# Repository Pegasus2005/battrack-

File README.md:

# 🏏 BatTrack — Universal Sports Implement Tracker

> **PCB Status: ✅ 39/39 connectivity checks passed — Fabrication ready**

A compact, open-source motion tracker for **cricket bats, baseball bats, badminton rackets, pickleball paddles**, tennis rackets, squash rackets, hockey sticks, and all bat/racket sports implements.

## ✅ Verified Connections (39/39)

| Block | Connections | Status |
|:---|:---|:---|
| USB-C (J1) | VBUS→VUSB, D+→USB_DP, D-→USB_DM, CC1/CC2 pulldowns | ✅ All 11 |
| TP4054 Charger (U3) | VUSB→pin4, VBAT→pin3, GND→pin2, CHRG_STAT, PROG | ✅ All 9 |
| SPI Bus (U1↔U2) | SCK, MISO, MOSI, CS, INT1 — all with F↔B vias | ✅ All 5 |
| WS2812B LED (D1) | VDD→VBAT, GND, DIN→LED_GPIO, DOUT→NC | ✅ All 4 |
| Power/Control | CHIP_EN, BTN_GPIO, ANT_RF, CC pulldowns | ✅ All 5 |
| Board specs | 22×16mm rect, 0.8mm, 2L, GND pour ×2 | ✅ All 4 |

---

## 📐 Hardware Overview

| Spec | Value |
|:---|:---|
| Board size | 22 × 16mm (+ 2mm USB-C slot) |
| Layers | 2-layer PCB |
| Thickness | 0.8mm FR4 |
| MCU | ESP32-C3FN4 (RISC-V, BLE 5.0, USB built-in) |
| IMU | QMI8658C (6-axis: ±16g accel + ±2048°/s gyro) |
| Connectivity | BLE 5.0 to smartphone |
| USB | USB-C (charge + firmware flash, no extra chip needed) |
| LED | WS2812B-2020 RGB (addressable, 1-wire) |
| Battery | LiPo via JST-PH pads (TP4054 charger, 50mA) |
| Button | Tactile boot/user button |

---

## 🎯 What It Tracks

| Sport | Metrics |
|:---|:---|
| Cricket | Bat swing speed, shot direction, impact force |
| Baseball | Swing arc, bat speed, impact detection |
| Badminton | Racket head speed, smash/drop/clear classification |
| Pickleball | Dink vs drive, spin, swing pattern |
| Tennis | Serve speed, groundstroke direction |
| Squash / Table Tennis | Stroke classification, wrist snap timing |

---

## 📦 Bill of Materials

| Ref | Component | Value | Package | Est. Cost |
|:---|:---|:---|:---|:---|
| U1 | ESP32-C3FN4 | MCU + BLE | QFN-32 | $1.50 |
| U2 | QMI8658C | 6-axis IMU | LGA-14 | $0.95 |
| U3 | TP4054 | LiPo charger | SOT-23-5 | $0.12 |
| J1 | USB-C | Charge + flash | SMD | $0.18 |
| D1 | WS2812B-2020 | RGB LED | 2020 | $0.05 |
| ANT1 | Chip antenna | 2.4GHz | 1608 | $0.35 |
| SW1 | Tact button | Boot/user | SMD | $0.10 |
| R2,R3 | 5.1KΩ | USB CC | 0402 | $0.01 ea |
| R4 | 20KΩ | Charge current | 0402 | $0.01 |
| R5,R6 | 10KΩ | EN / Boot | 0402 | $0.01 ea |
| C1,C3,C8,C9 | 100nF | Bypass | 0402 | $0.01 ea |
| C2 | 10uF | Bulk cap | 0402 | $0.04 |
| C4,C5 | 1uF | VUSB/VBAT | 0402 | $0.02 ea |
| **Total BOM** | | | | **~$3.50/board** |

---

## 🗂️ Repository Structure

```
hardware/
  sport_tracker/
    sport_tracker.kicad_pcb     ← PCB layout (KiCad 10)
    sport_tracker.kicad_sch     ← Schematic (KiCad 10)
    sport_tracker_gerbers.zip   ← Ready to upload to JLCPCB/PCBWay
    bom.csv                     ← Bill of materials with pricing
    gerbers/                    ← Individual Gerber files (14 layers)
```

---

## 🏭 Fabrication

Upload `hardware/sport_tracker/sport_tracker_gerbers.zip` to:
- **[JLCPCB](https://jlcpcb.com)** — 5 boards ~$4 USD
- **[PCBWay](https://www.pcbway.com)** — 5 boards ~$5 USD

Settings: **2 layers, 0.8mm, HASL or ENIG, green soldermask**

---

## ⚡ Firmware Flashing

```bash
# Hold BOOT button while connecting USB-C
esptool.py --chip esp32c3 --port COMx write_flash 0x0 firmware.bin
```

No external USB-UART chip needed — ESP32-C3 has built-in USB Serial/JTAG.

---

## 📡 BLE Data Protocol

The board streams IMU data over BLE to a smartphone app:
- **Accel**: X/Y/Z at ±16g, 500Hz
- **Gyro**: X/Y/Z at ±2048°/s, 500Hz
- **Computed**: swing speed (°/s), impact timestamp, session stats

---

## 📄 License

Open source — MIT License. PCB design files free to use, modify, and manufacture.

---

*Designed with KiCad 10 | Fabricated by JLCPCB*

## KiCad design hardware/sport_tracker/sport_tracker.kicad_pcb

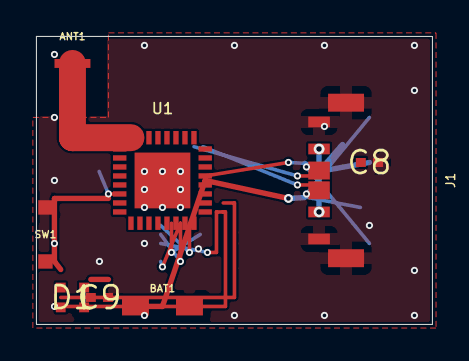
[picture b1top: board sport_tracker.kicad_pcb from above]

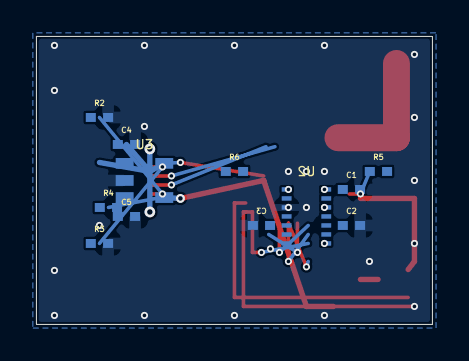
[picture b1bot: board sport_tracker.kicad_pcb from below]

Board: 2 copper layers, 22.0 x 16.0 mm, 20 parts (13 on the bottom side), 18 nets.

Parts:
ANT1: 2.4GHz; Antenna_2.4GHz
BAT1: LiPo_100mAh; BAT_Pads
C1, C3: 100nF; C_0402
C2: 10uF; C_0402
C4, C5: 1uF; C_0402
C8, C9: 100nF
D1: WS2812B-2020
J1: USB-C; USB_C_Charge
R2, R3: 5.1K; R_0402
R4: 20K; R_0402
R5, R6: 10K; R_0402
SW1: BTN; SW_TACT
U1: ESP32-C3FH4; ESP32-C3FN4_QFN32
U2: QMI8658A; QMI8658C_LGA14
U3: TP4054; TP4054_SOT235

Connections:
ANT_RF: ANT1.1, U1.1
BTN_GPIO: R6.2, SW1.1, U1.11
CC1: J1.A5, R2.1
CC2: J1.B5, R3.1
CHIP_EN: R5.2, U1.30
CHRG_STAT: U1.13, U3.1
GND: ANT1.2, BAT1.-, C1.2, C2.2, C3.2, C4.2, C5.2, C8.2, C9.2, D1.3, J1.A1, J1.B12, J1.SH1, J1.SH2, R2.2, R3.2, R4.2, SW1.2, U1.33, U2.5, U2.12, U3.2
IMU_INT1: U1.5, U2.6
LED_GPIO: D1.4, U1.10
PROG: R4.1, U3.5
SPI_CS: U1.4, U2.11
SPI_MISO: U1.6, U2.2
SPI_MOSI: U1.9, U2.4
SPI_SCK: U1.7, U2.3
USB_DM: J1.A7, J1.B7, U1.17
USB_DP: J1.A6, J1.B6, U1.18
VBAT: BAT1.+, C1.1, C2.1, C3.1, C5.1, C9.1, D1.1, R5.1, R6.1, U1.2, U1.3, U1.8, U1.16, U1.20, U1.27, U2.1, U2.10, U3.3
VUSB: C4.1, C8.1, J1.A4, J1.B4, U3.4

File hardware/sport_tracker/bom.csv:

Ref,Value,Layer,Package,Manufacturer,MPN,Price_ea_USD
ANT1,2.4GHz,F.Cu,1608,Yageo,ANT1608F2450A00A,0.35
BAT1,LiPo_100mAh,F.Cu,SMD,Generic,JST-PH-2-SMD,0.08
C1,100nF,B.Cu,0402,Samsung,CL05B104KO5NNNC,0.01
C2,10uF,B.Cu,0402,Samsung,CL05A106MQ5NUNC,0.04
C3,100nF,B.Cu,0402,Samsung,CL05B104KO5NNNC,0.01
C4,1uF,B.Cu,0402,Samsung,CL05A105KO5NNNC,0.02
C5,1uF,B.Cu,0402,Samsung,CL05A105KO5NNNC,0.02
C8,100nF,B.Cu,0402,Samsung,CL05B104KO5NNNC,0.01
C9,100nF,F.Cu,0402,Samsung,CL05B104KO5NNNC,0.01
D1,WS2812B-2020,F.Cu,2020,Worldsemi,WS2812B-2020,0.05
J1,USB-C,F.Cu,SMD,Korean Hroparts,TYPE-C-31-M-12,0.18
R2,5.1K,B.Cu,0402,Generic,RC0402FR-075K1L,0.01
R3,5.1K,B.Cu,0402,Generic,RC0402FR-075K1L,0.01
R4,20K,B.Cu,0402,Generic,RC0402FR-0720KL,0.01
R5,10K,B.Cu,0402,Generic,RC0402FR-0710KL,0.01
R6,10K,B.Cu,0402,Generic,RC0402FR-0710KL,0.01
SW1,BTN,F.Cu,SMD,C&K,PTS525SK15SMTR2LFS,0.10
U1,ESP32-C3FN4,F.Cu,QFN-32,Espressif,ESP32-C3FN4,1.50
U2,QMI8658C,B.Cu,LGA-14,QST,QMI8658C,0.95
U3,TP4054,B.Cu,SOT-23-5,NanJing Qinheng,TP4054-42-SOT23-5,0.12

# Total BOM cost per board (components only): $3.50 USD
# PCB fab cost (JLCPCB 5pcs 22x16mm 2L 0.8mm): ~$2-4 USD per board
# Estimated total per board (BOM+PCB): ~$6.50 USD
